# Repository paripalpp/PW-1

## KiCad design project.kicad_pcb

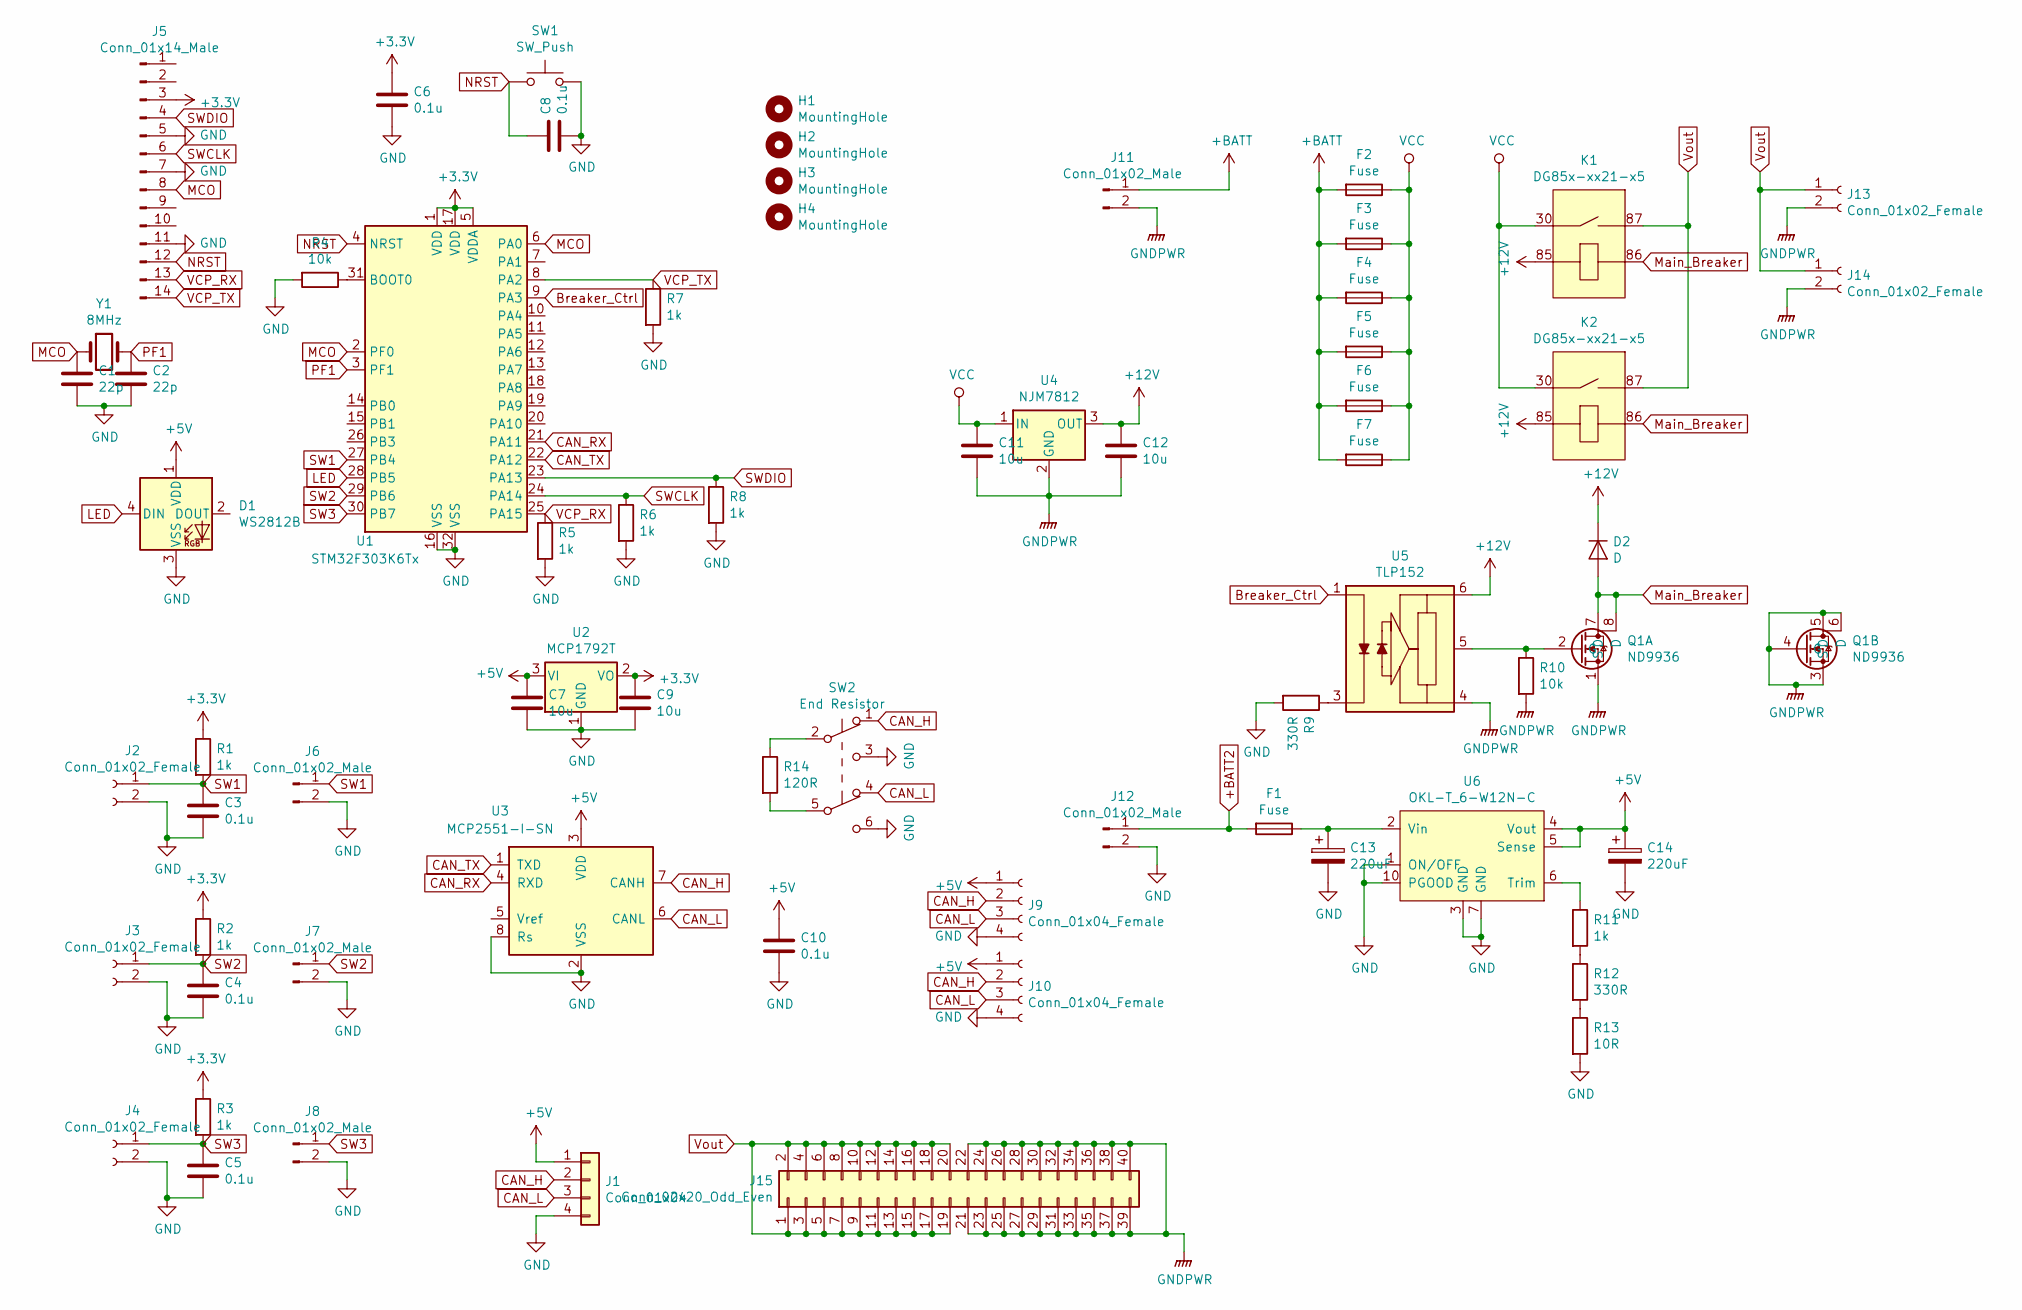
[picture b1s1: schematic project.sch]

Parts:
C1, C2: 22p; C_0603_1608Metric
C3, C4, C5, C6, C8, C10: 0.1u; C_0603_1608Metric
C7, C9, C11, C12: 10u; C_0805_2012Metric
C13, C14: 220uF; CP_Elec_10x10
D1: WS2812B; LED_WS2812B_PLCC4_5.0x5.0mm_P3.2mm
D2: D; D_SOD-123F
F1, F2, F3, F4, F5, F6, F7: Fuse; Pudenz_FuseHolder
H1, H2, H3, H4: MountingHole; MountingHole_3.2mm_M3_Pad_Via
J1: Conn_01x04; PinSocket_1x04_P2.54mm_Vertical
J2, J3, J4: Conn_01x02_Female; S02B-XASS-1
J5: Conn_01x14_Male; PinHeader_2x07_P1.27mm_Vertical
J6, J7, J8: Conn_01x02_Male; PinHeader_1x02_P2.54mm_Vertical
J9, J10: Conn_01x04_Female; S04B-XASK-1
J11, J12: Conn_01x02_Male; T_conector_male
J13, J14: Conn_01x02_Female; T_connector_femla
J15: Conn_02x20_Odd_Even; PinSocket_2x20_P2.54mm_Vertical
K1, K2: DG85x-xx21-x5
Q1: ND9936; SO-8_5.3x6.2mm_P1.27mm
R1, R2, R3, R5, R6, R7, R8, R11: 1k; R_0603_1608Metric
R4, R10: 10k; R_0603_1608Metric
R9, R12: 330R; R_0603_1608Metric
R13: 10R; R_0603_1608Metric
R14: 120R; R_0603_1608Metric
SW1: SW_Push; switch_smd
SW2: End Resistor; IS-2235
U1: STM32F303K6Tx; LQFP-32_7x7mm_P0.8mm
U2: MCP1792T; SOT-23
U3: MCP2551-I-SN; SOIC-8_3.9x4.9mm_P1.27mm
U4: NJM7812; TO-252-2
U5: TLP152; SO-6_4.4x3.6mm_P1.27mm
U6: OKL-T_6-W12N-C; OKL_T6_W12
Y1: 8MHz; Crystal_HC50_Vertical

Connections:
+3V3: C6.1, C9.1, J5.3, R1.1, R2.1, R3.1, U1.1 (VDD), U1.5 (VDDA), U1.17 (VDD), U2.2 (VO)
+5V: C7.1, C10.1, C14.1, D1.1 (VDD), J1.1, J9.1, J10.1, U2.3 (VI), U3.3 (VDD), U6.4 (Vout), U6.5 (Sense)
+12V: C12.1, D2.1 (K), K1.85, K2.85, U4.3 (OUT), U5.6 (Vcc)
+BATT: F2.2, F3.2, F4.2, F5.2, F6.2, F7.2, J11.1
+BATT2: F1.2, J12.1
Breaker_Ctrl: U1.9 (PA3), U5.1 (A)
CAN_H: J1.2, J9.2, J10.2, SW2.1 (A), U3.7 (CANH)
CAN_L: J1.3, J9.3, J10.3, SW2.4 (A), U3.6 (CANL)
CAN_RX: U1.21 (PA11), U3.4 (RXD)
CAN_TX: U1.22 (PA12), U3.1 (TXD)
GND: C1.2, C2.2, C3.2, C4.2, C5.2, C6.2, C7.2, C8.2, C9.2, C10.2, C13.2, C14.2, D1.3 (VSS), J1.4, J2.2, J3.2, J4.2, J5.5, J5.7, J5.11, J6.2, J7.2, J8.2, J9.4, J10.4, J12.2, R4.2, R5.2, R6.2, R7.2, R8.2, R9.2, R13.2, SW1.2, SW2.3 (C), SW2.6 (C), U1.16 (VSS), U1.32 (VSS), U2.1 (GND), U3.2 (VSS), U3.8 (Rs), U6.1 (ON/OFF), U6.3 (GND), U6.7 (GND), U6.10 (PGOOD)
GNDPWR: C11.2, C12.2, J11.2, J13.2, J14.2, J15.21, J15.22, J15.23, J15.24, J15.25, J15.26, J15.27, J15.28, J15.29, J15.30, J15.31, J15.32, J15.33, J15.34, J15.35, J15.36, J15.37, J15.38, J15.39, J15.40, Q1.1 (S), Q1.3 (S), Q1.4 (G), Q1.5 (D), Q1.6 (D), R10.2, U4.2 (GND), U5.4 (GND)
LED: D1.4 (DIN), U1.28 (PB5)
MCO: C1.1, J5.8, U1.2 (PF0), U1.6 (PA0), Y1.1
Main_Breaker: D2.2 (A), K1.86, K2.86, Q1.7 (D), Q1.8 (D)
NRST: C8.1, J5.12, SW1.1, U1.4 (NRST)
unnamed: C13.1, F1.1, U6.2 (Vin)
unnamed: Q1.2 (G), R10.1, U5.5 (Vo)
unnamed: R4.1, U1.31 (BOOT0)
unnamed: R9.1, U5.3 (C)
unnamed: R11.1, U6.6 (Trim)
unnamed: R11.2, R12.1
unnamed: R12.2, R13.1
unnamed: R14.1, SW2.2 (B)
unnamed: R14.2, SW2.5 (B)
PF1: C2.1, U1.3 (PF1), Y1.2
SW1: C3.1, J2.1, J6.1, R1.2, U1.27 (PB4)
SW2: C4.1, J3.1, J7.1, R2.2, U1.29 (PB6)
SW3: C5.1, J4.1, J8.1, R3.2, U1.30 (PB7)
SWCLK: J5.6, R6.1, U1.24 (PA14)
SWDIO: J5.4, R8.1, U1.23 (PA13)
VCC: C11.1, F2.1, F3.1, F4.1, F5.1, F6.1, F7.1, K1.30, K2.30, U4.1 (IN)
VCP_RX: J5.13, R5.1, U1.25 (PA15)
VCP_TX: J5.14, R7.1, U1.8 (PA2)
Vout: J13.1, J14.1, J15.1, J15.2, J15.3, J15.4, J15.5, J15.6, J15.7, J15.8, J15.9, J15.10, J15.11, J15.12, J15.13, J15.14, J15.15, J15.16, J15.17, J15.18, J15.19, J15.20, K1.87, K2.87

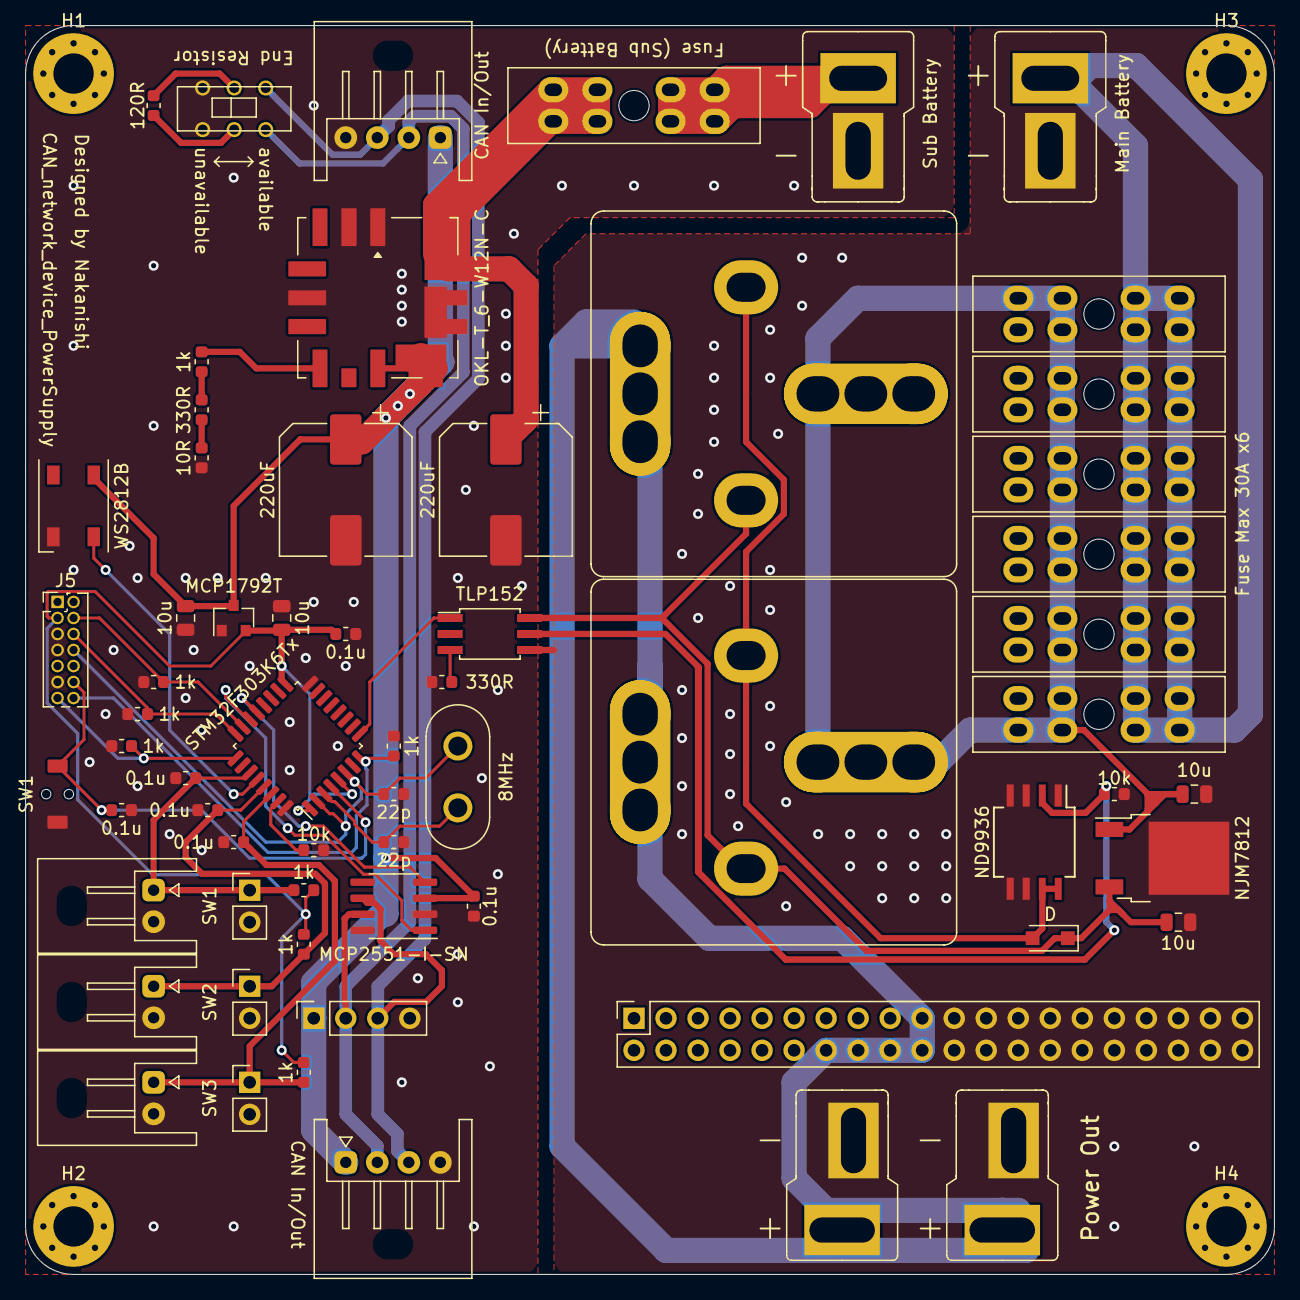
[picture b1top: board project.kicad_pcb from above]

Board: 2 copper layers, 99.1 x 99.1 mm, 68 parts (0 on the bottom side), 35 nets.
